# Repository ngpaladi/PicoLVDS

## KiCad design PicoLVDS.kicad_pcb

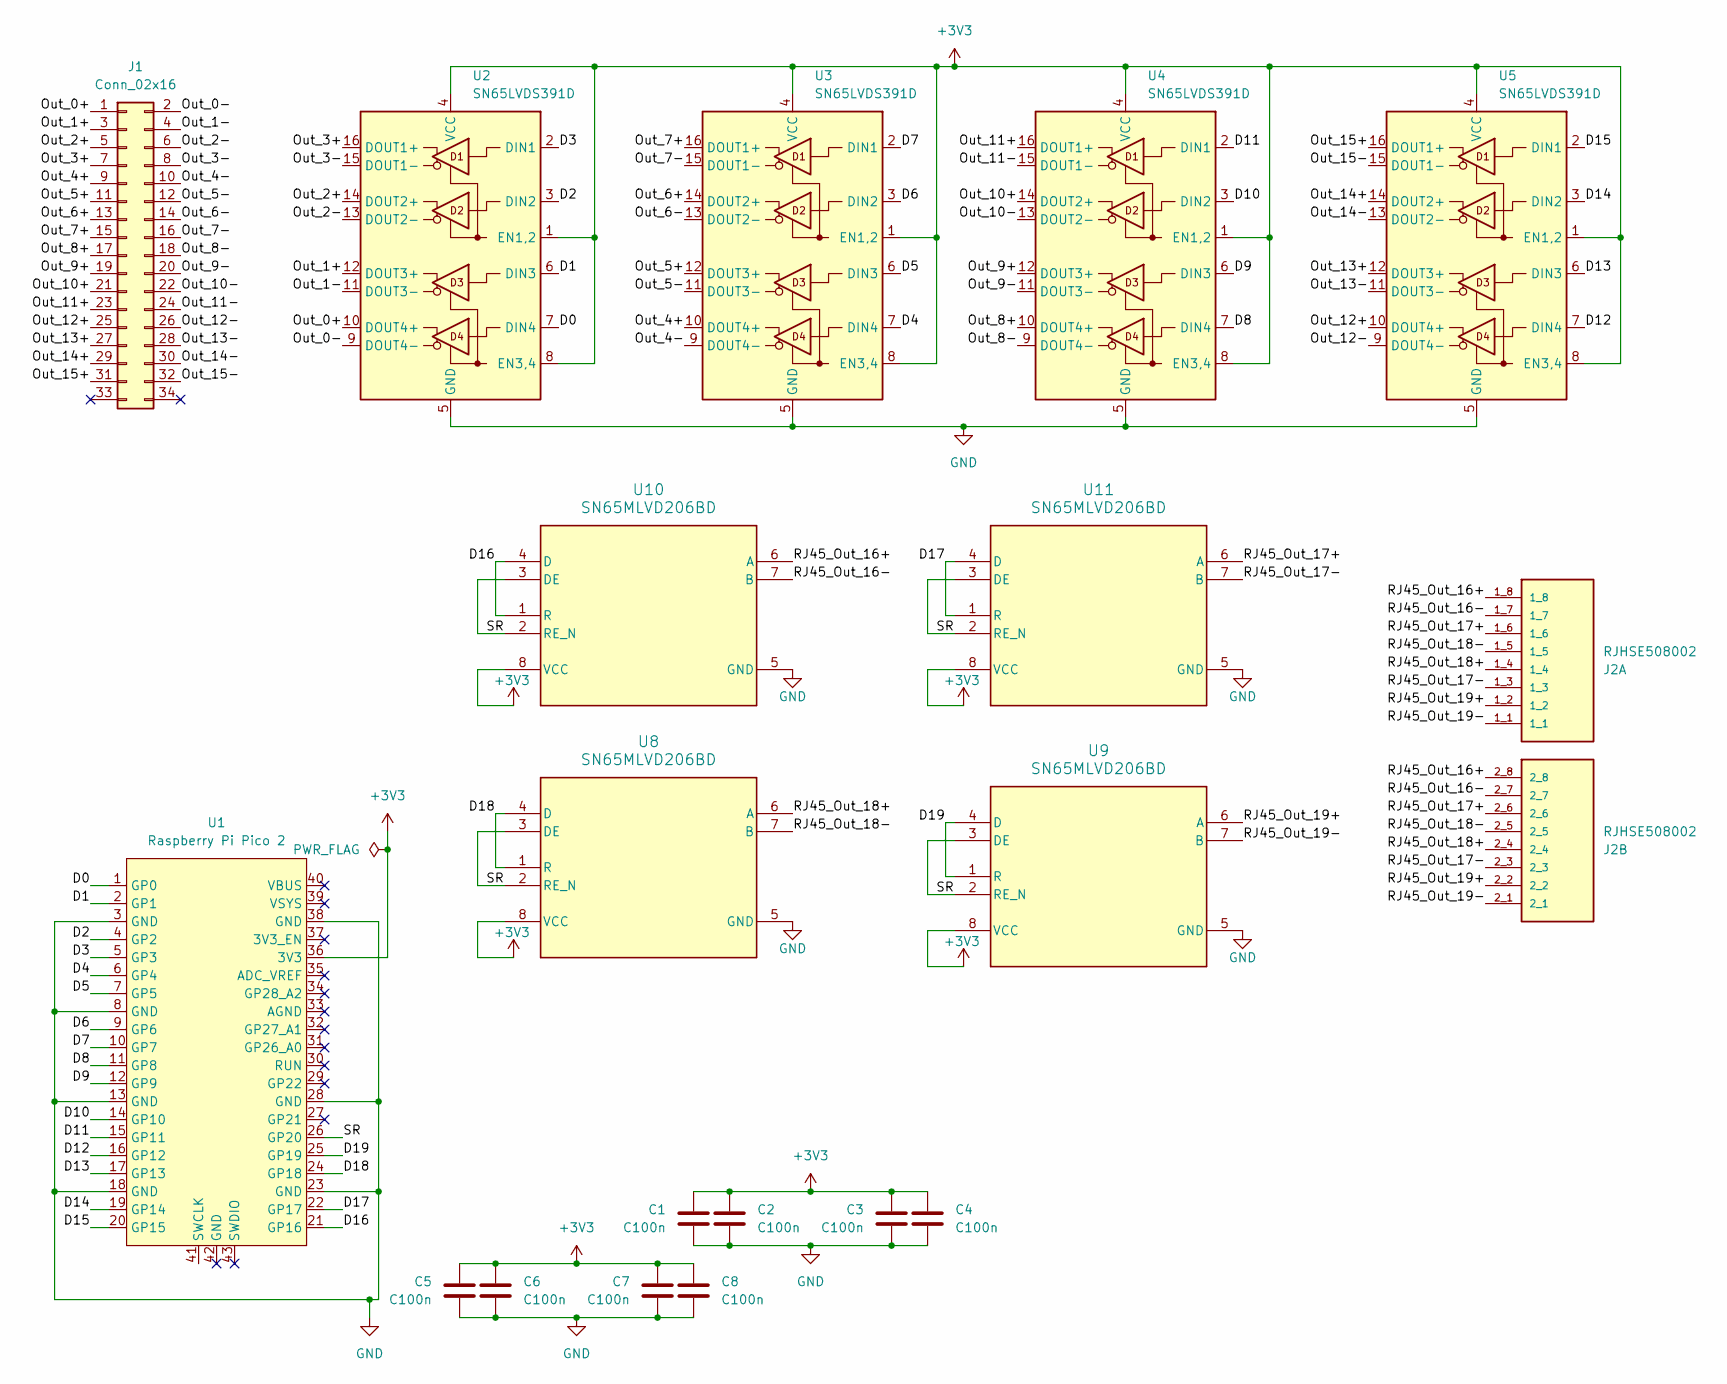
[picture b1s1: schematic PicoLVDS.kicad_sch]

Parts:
C1, C2, C3, C4, C5, C6, C7, C8: C100n; C_0402_1005Metric_Pad0.74x0.62mm_HandSolder
J1: Conn_02x16; PinHeader_2x17_P2.54mm_Vertical_ECL
J2: RJHSE508002; AMPHENOL_RJHSE508002; PARTREV E
U1: Raspberry Pi Pico 2; RasPi_Pico_2_SMD
U2, U3, U4, U5: SN65LVDS391D; SOIC-16_3.9x9.9mm_P1.27mm
U8, U9, U10, U11: SN65MLVD206BD; D0008A_N

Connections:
+3V3: C1.1, C2.1, C3.1, C4.1, C5.1, C6.1, C7.1, C8.1, U1.36 (3V3), U2.1 (EN1,2), U2.4 (VCC), U2.8 (EN3,4), U3.1 (EN1,2), U3.4 (VCC), U3.8 (EN3,4), U4.1 (EN1,2), U4.4 (VCC), U4.8 (EN3,4), U5.1 (EN1,2), U5.4 (VCC), U5.8 (EN3,4), U8.8 (VCC), U9.8 (VCC), U10.8 (VCC), U11.8 (VCC)
/D0: U1.1 (GP0), U2.7 (DIN4)
/D1: U1.2 (GP1), U2.6 (DIN3)
/D2: U1.4 (GP2), U2.3 (DIN2)
/D3: U1.5 (GP3), U2.2 (DIN1)
/D4: U1.6 (GP4), U3.7 (DIN4)
/D5: U1.7 (GP5), U3.6 (DIN3)
/D6: U1.9 (GP6), U3.3 (DIN2)
/D7: U1.10 (GP7), U3.2 (DIN1)
/D8: U1.11 (GP8), U4.7 (DIN4)
/D9: U1.12 (GP9), U4.6 (DIN3)
/D10: U1.14 (GP10), U4.3 (DIN2)
/D11: U1.15 (GP11), U4.2 (DIN1)
/D12: U1.16 (GP12), U5.7 (DIN4)
/D13: U1.17 (GP13), U5.6 (DIN3)
/D14: U1.19 (GP14), U5.3 (DIN2)
/D15: U1.20 (GP15), U5.2 (DIN1)
/D16: U1.21 (GP16), U10.1 (R), U10.4 (D)
/D17: U1.22 (GP17), U11.1 (R), U11.4 (D)
/D18: U1.24 (GP18), U8.1 (R), U8.4 (D)
/D19: U1.25 (GP19), U9.1 (R), U9.4 (D)
/Out_0+: J1.1, U2.10 (DOUT4+)
/Out_0-: J1.2, U2.9 (DOUT4-)
/Out_1+: J1.3, U2.12 (DOUT3+)
/Out_1-: J1.4, U2.11 (DOUT3-)
/Out_2+: J1.5, U2.14 (DOUT2+)
/Out_2-: J1.6, U2.13 (DOUT2-)
/Out_3+: J1.7, U2.16 (DOUT1+)
/Out_3-: J1.8, U2.15 (DOUT1-)
/Out_4+: J1.9, U3.10 (DOUT4+)
/Out_4-: J1.10, U3.9 (DOUT4-)
/Out_5+: J1.11, U3.12 (DOUT3+)
/Out_5-: J1.12, U3.11 (DOUT3-)
/Out_6+: J1.13, U3.14 (DOUT2+)
/Out_6-: J1.14, U3.13 (DOUT2-)
/Out_7+: J1.15, U3.16 (DOUT1+)
/Out_7-: J1.16, U3.15 (DOUT1-)
/Out_8+: J1.17, U4.10 (DOUT4+)
/Out_8-: J1.18, U4.9 (DOUT4-)
/Out_9+: J1.19, U4.12 (DOUT3+)
/Out_9-: J1.20, U4.11 (DOUT3-)
/Out_10+: J1.21, U4.14 (DOUT2+)
/Out_10-: J1.22, U4.13 (DOUT2-)
/Out_11+: J1.23, U4.16 (DOUT1+)
/Out_11-: J1.24, U4.15 (DOUT1-)
/Out_12+: J1.25, U5.10 (DOUT4+)
/Out_12-: J1.26, U5.9 (DOUT4-)
/Out_13+: J1.27, U5.12 (DOUT3+)
/Out_13-: J1.28, U5.11 (DOUT3-)
/Out_14+: J1.29, U5.14 (DOUT2+)
/Out_14-: J1.30, U5.13 (DOUT2-)
/Out_15+: J1.31, U5.16 (DOUT1+)
/Out_15-: J1.32, U5.15 (DOUT1-)
/RJ45_Out_16+: J2.1_8, J2.2_8, U10.6 (A)
/RJ45_Out_16-: J2.1_7, J2.2_7, U10.7 (B)
/RJ45_Out_17+: J2.1_6, J2.2_6, U11.6 (A)
/RJ45_Out_17-: J2.1_3, J2.2_3, U11.7 (B)
/RJ45_Out_18+: J2.1_4, J2.2_4, U8.6 (A)
/RJ45_Out_18-: J2.1_5, J2.2_5, U8.7 (B)
/RJ45_Out_19+: J2.1_2, J2.2_2, U9.6 (A)
/RJ45_Out_19-: J2.1_1, J2.2_1, U9.7 (B)
/SR: U1.26 (GP20), U8.2 (RE_N), U8.3 (DE), U9.2 (RE_N), U9.3 (DE), U10.2 (RE_N), U10.3 (DE), U11.2 (RE_N), U11.3 (DE)
GND: C1.2, C2.2, C3.2, C4.2, C5.2, C6.2, C7.2, C8.2, U1.3 (GND), U1.8 (GND), U1.13 (GND), U1.18 (GND), U1.23 (GND), U1.28 (GND), U1.38 (GND), U2.5 (GND), U3.5 (GND), U4.5 (GND), U5.5 (GND), U8.5 (GND), U9.5 (GND), U10.5 (GND), U11.5 (GND)

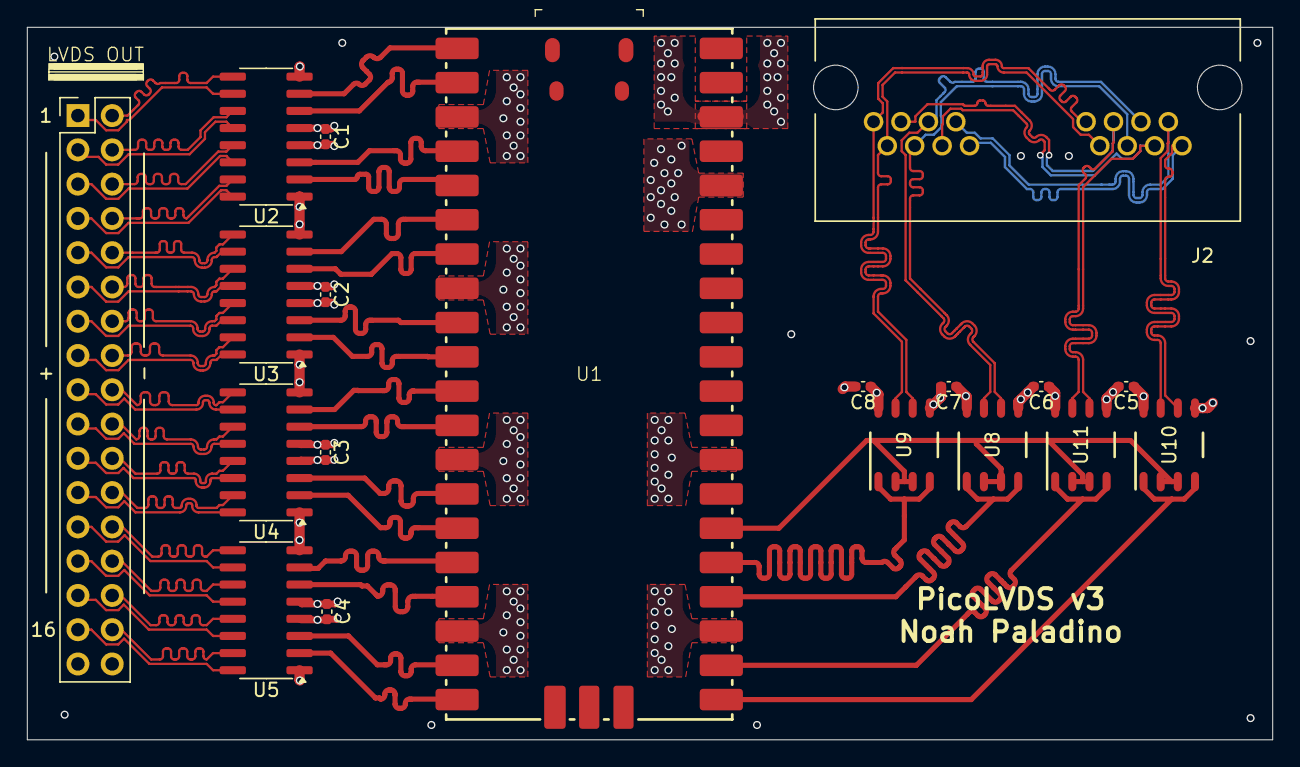
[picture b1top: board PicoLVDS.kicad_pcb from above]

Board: 4 copper layers, 92.3 x 52.8 mm, 19 parts (0 on the bottom side), 63 nets.

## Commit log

2025-02-21 KiCad 9 Update
2025-03-11 nomacro
2025-03-14 Schematic v2
2025-03-18 Switch to SMT footprint
2025-03-18 Switch Footprints
2025-03-21 Add HTML BOM
2025-05-02 Add Stencil Frame
